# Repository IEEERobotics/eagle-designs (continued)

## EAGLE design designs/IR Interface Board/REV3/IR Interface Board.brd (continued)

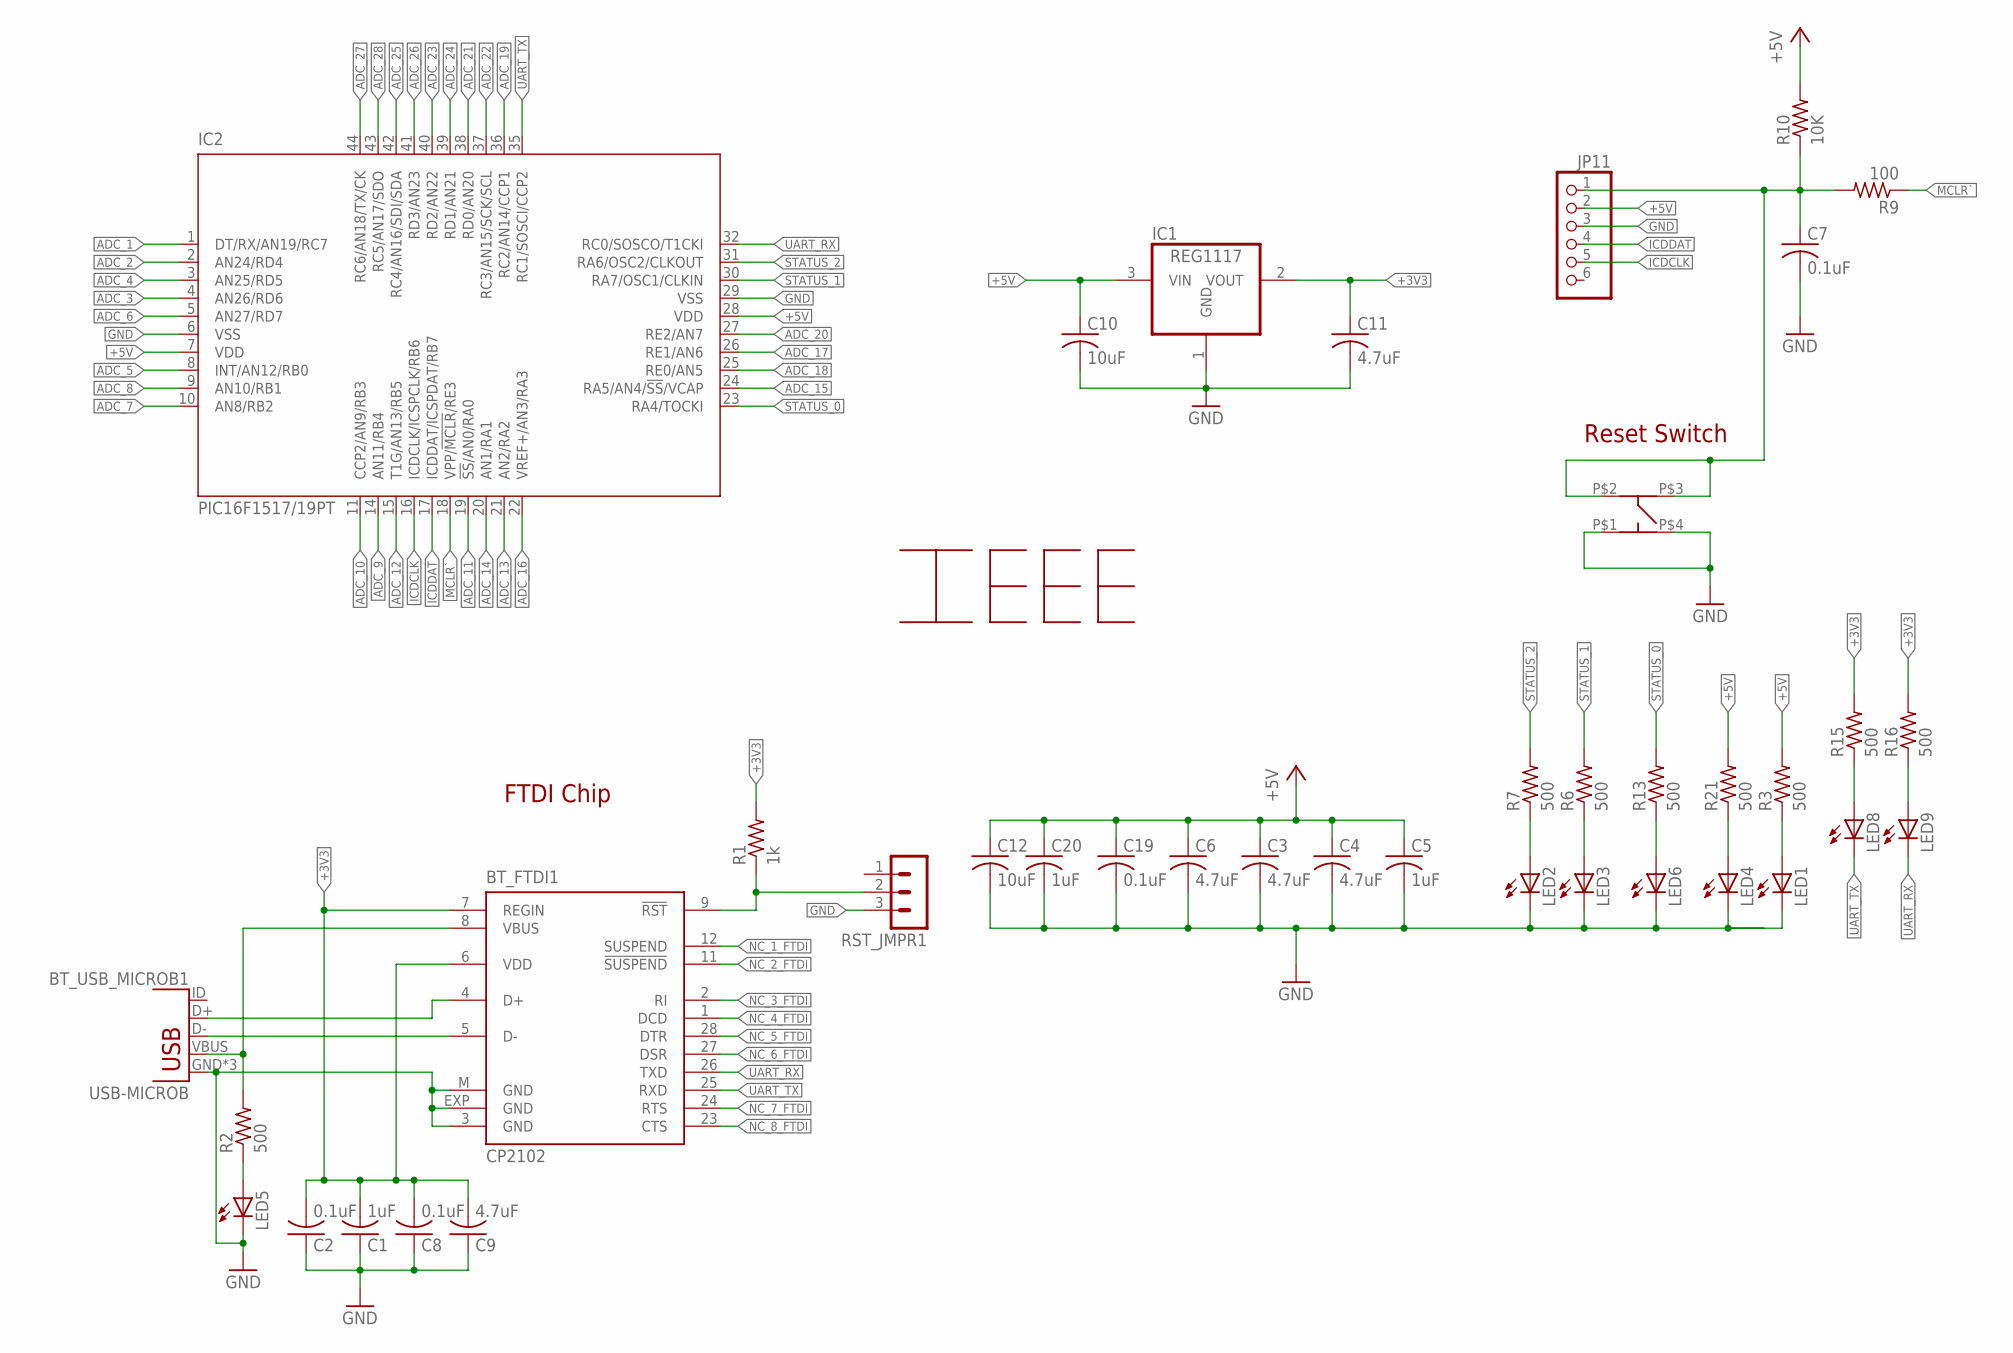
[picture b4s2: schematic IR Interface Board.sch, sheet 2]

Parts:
BT_FTDI1: CP2102; MLP28
BT_USB_MICROB1: USB-MICROB
C1, C5, C20: 1uF; C0805
C2, C7, C8, C19: 0.1uF; C0805
C3, C4, C6, C9, C11: 4.7uF; C0805
C10, C12: 10uF; C0805
IC1: REG1117; SOT223
IC2: PIC16F1517/19PT; TQFP44
JP11: PINHD-1X6/90; 1X06/90
LED1, LED2, LED3, LED4, LED5, LED6, LED8, LED9: LEDSML0603; SML0603
R1: 1k; R0805
R2, R3, R6, R7, R13, R15, R16, R21: 500; R0805
R9: 100; R0805
R10: 10K; R0805
RST_JMPR1: MA03-1
TOUCH_RESET: RESET; MC32882_FINAL
U$1: LOGO; IEEE-LOGO

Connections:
+3V3: BT_FTDI1.6 (VDD), BT_FTDI1.7 (REGIN), C1.2, C2.2, C8.2, C9.2, C11.1, IC1.2 (VOUT), R1.2, R15.2, R16.2
+5V: C3.1, C4.1, C5.1, C6.1, C10.1, C12.1, C19.1, C20.1, IC1.3 (VIN), IC2.7 (VDD), IC2.28 (VDD), JP11.2, R3.2, R10.2, R21.2; also elsewhere on the board
ADC_1: IC2.1 (DT/RX/AN19/RC7); also elsewhere on the board
ADC_2: IC2.2 (AN24/RD4); also elsewhere on the board
ADC_3: IC2.4 (AN26/RD6); also elsewhere on the board
ADC_4: IC2.3 (AN25/RD5); also elsewhere on the board
ADC_5: IC2.8 (INT/AN12/RB0); also elsewhere on the board
ADC_6: IC2.5 (AN27/RD7); also elsewhere on the board
ADC_7: IC2.10 (AN8/RB2); also elsewhere on the board
ADC_8: IC2.9 (AN10/RB1); also elsewhere on the board
ADC_9: IC2.14 (AN11/RB4); also elsewhere on the board
ADC_10: IC2.11 (CCP2/AN9/RB3); also elsewhere on the board
ADC_11: IC2.19 (!SS!/AN0/RA0); also elsewhere on the board
ADC_12: IC2.15 (T1G/AN13/RB5); also elsewhere on the board
ADC_13: IC2.21 (AN2/RA2); also elsewhere on the board
ADC_14: IC2.20 (AN1/RA1); also elsewhere on the board
ADC_15: IC2.24 (RA5/AN4/!SS!/VCAP); also elsewhere on the board
ADC_16: IC2.22 (VREF+/AN3/RA3); also elsewhere on the board
ADC_17: IC2.26 (RE1/AN6); also elsewhere on the board
ADC_18: IC2.25 (RE0/AN5); also elsewhere on the board
ADC_19: IC2.36 (RC2/AN14/CCP1); also elsewhere on the board
ADC_20: IC2.27 (RE2/AN7); also elsewhere on the board
ADC_21: IC2.38 (RD0/AN20); also elsewhere on the board
ADC_22: IC2.37 (RC3/AN15/SCK/SCL); also elsewhere on the board
ADC_23: IC2.40 (RD2/AN22); also elsewhere on the board
ADC_24: IC2.39 (RD1/AN21); also elsewhere on the board
ADC_25: IC2.42 (RC4/AN16/SDI/SDA); also elsewhere on the board
ADC_26: IC2.41 (RD3/AN23); also elsewhere on the board
ADC_27: IC2.44 (RC6/AN18/TX/CK); also elsewhere on the board
ADC_28: IC2.43 (RC5/AN17/SDO); also elsewhere on the board
BT_D+1: BT_FTDI1.4 (D+), BT_USB_MICROB1.D+
BT_D-1: BT_FTDI1.5 (D-), BT_USB_MICROB1.D-
GND: BT_FTDI1.3 (GND), BT_FTDI1.EXP (GND), BT_FTDI1.M (GND), BT_USB_MICROB1.GND, BT_USB_MICROB1.MT1 (GND), BT_USB_MICROB1.MT2 (GND), C1.1, C2.1, C3.2, C4.2, C5.2, C6.2, C7.2, C8.1, C9.1, C10.2, C11.2, C12.2, C19.2, C20.2, IC1.1 (GND), IC2.6 (VSS), IC2.29 (VSS), JP11.3, LED1.C, LED2.C, LED3.C, LED4.C, LED5.C, LED6.C, RST_JMPR1.3, TOUCH_RESET.P$1 (P1), TOUCH_RESET.P$4 (P4); also elsewhere on the board
ICDCLK: IC2.16 (ICDCLK/ICSPCLK/RB6), JP11.5
ICDDAT: IC2.17 (ICDDAT/ICSPDAT/RB7), JP11.4
MCLR: C7.1, JP11.1, R9.2, R10.1, TOUCH_RESET.P$2 (P2), TOUCH_RESET.P$3 (P3)
MCLR`: IC2.18 (VPP/!MCLR!/RE3), R9.1
unnamed: LED3.A, R6.1
unnamed: BT_FTDI1.9 (!RST), R1.1, RST_JMPR1.2
unnamed: LED6.A, R13.1
unnamed: LED1.A, R3.1
unnamed: LED2.A, R7.1
unnamed: LED4.A, R21.1
unnamed: LED8.A, R15.1
unnamed: LED9.A, R16.1
unnamed: LED5.A, R2.1
NC_1_FTDI: BT_FTDI1.12 (SUSPEND)
NC_2_FTDI: BT_FTDI1.11 (!SUSPEND)
NC_3_FTDI: BT_FTDI1.2 (RI)
NC_4_FTDI: BT_FTDI1.1 (DCD)
NC_5_FTDI: BT_FTDI1.28 (DTR)
NC_6_FTDI: BT_FTDI1.27 (DSR)
NC_7_FTDI: BT_FTDI1.24 (RTS)
NC_8_FTDI: BT_FTDI1.23 (CTS)
STATUS_0: IC2.23 (RA4/TOCKI), R13.2
STATUS_1: IC2.30 (RA7/OSC1/CLKIN), R6.2
STATUS_2: IC2.31 (RA6/OSC2/CLKOUT), R7.2
UART_RX: BT_FTDI1.26 (TXD), IC2.32 (RC0/SOSCO/T1CKI), LED9.C
UART_TX: BT_FTDI1.25 (RXD), IC2.35 (RC1/SOSCI/CCP2), LED8.C
VBUS: BT_FTDI1.8 (VBUS), BT_USB_MICROB1.VBUS, R2.2; also elsewhere on the board

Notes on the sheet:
Reset Switch
FTDI Chip

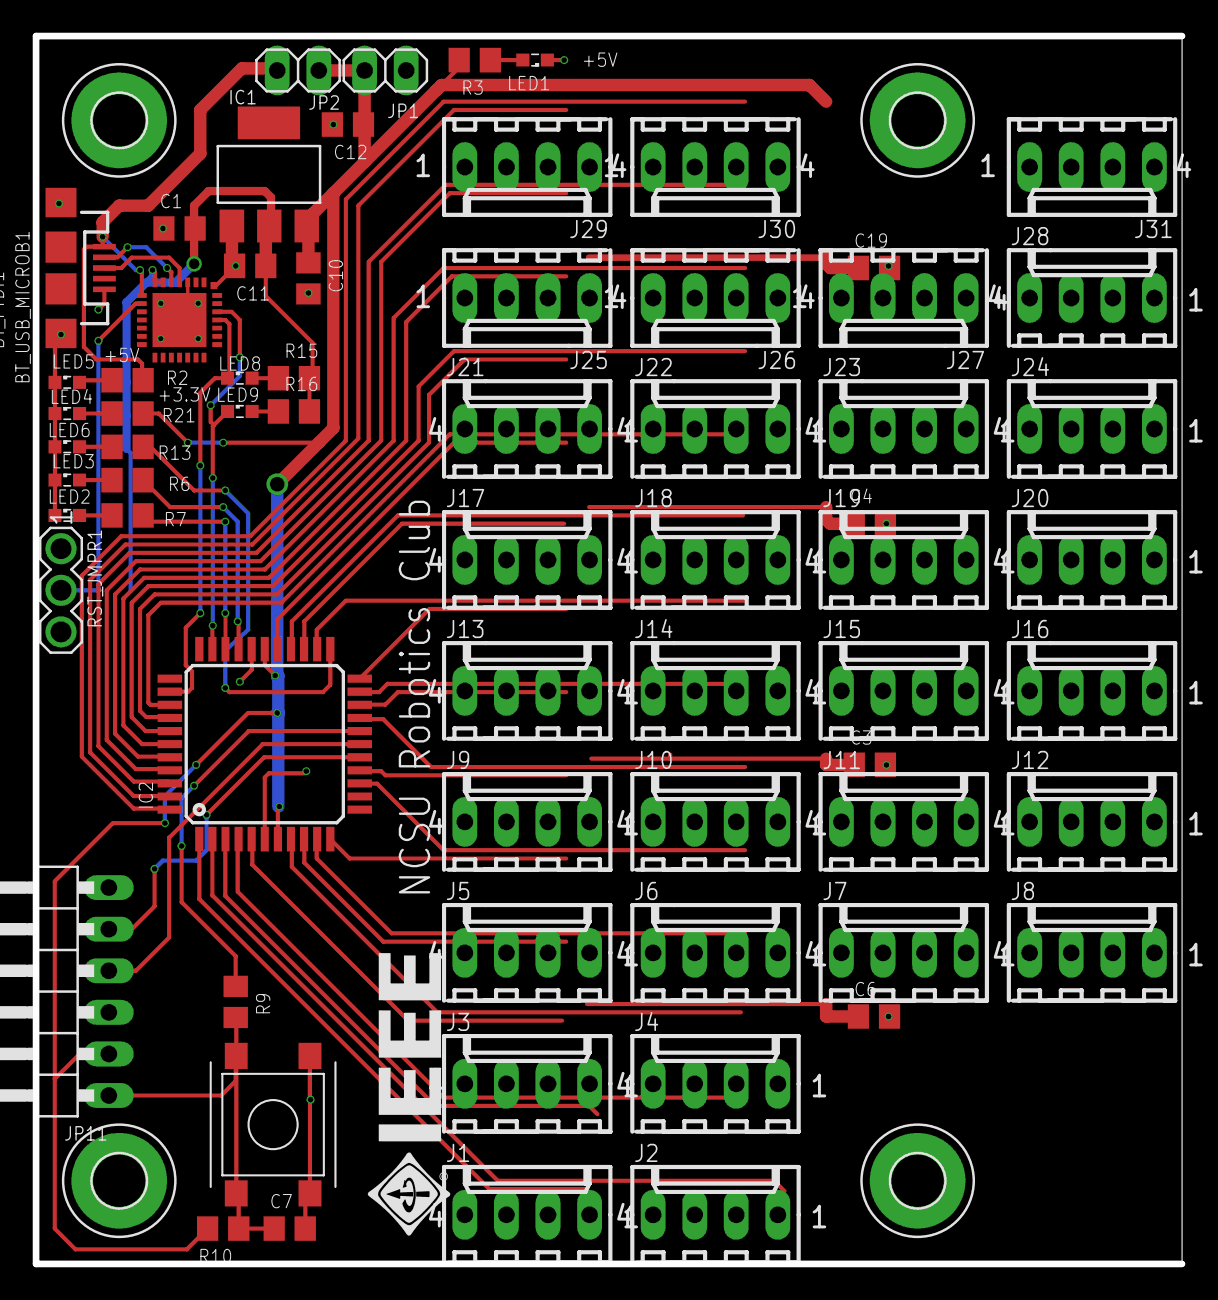
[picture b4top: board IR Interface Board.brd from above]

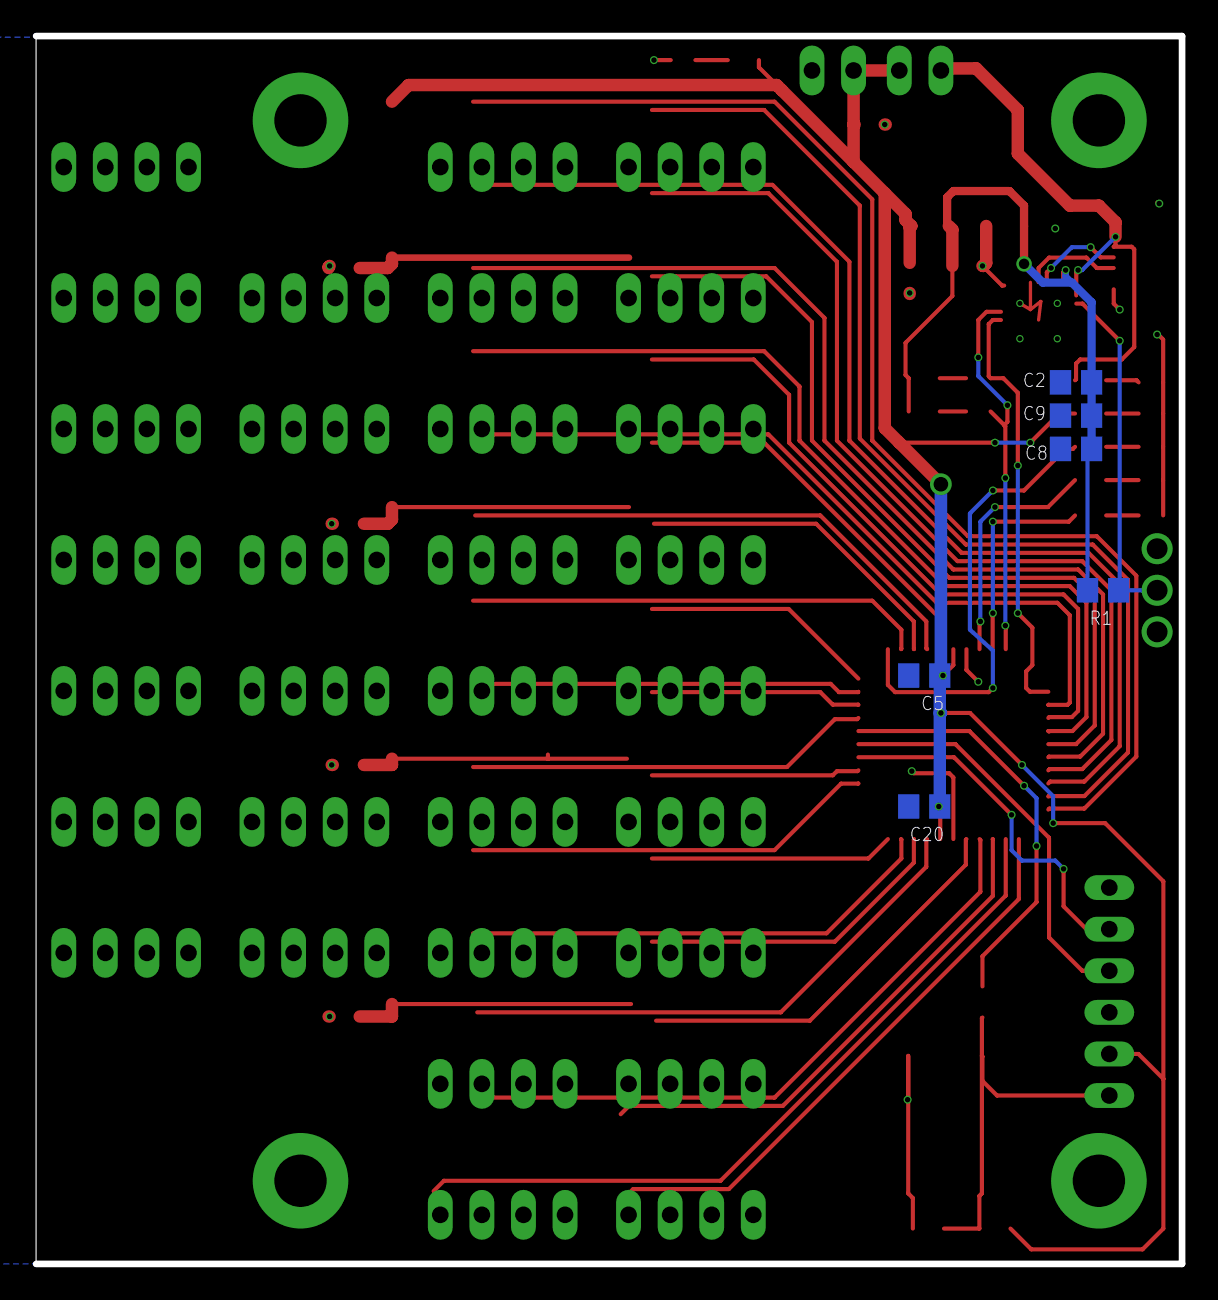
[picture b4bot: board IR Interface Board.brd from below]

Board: 2 copper layers, 70.0 x 75.0 mm, 78 parts (6 on the bottom side), 52 nets.

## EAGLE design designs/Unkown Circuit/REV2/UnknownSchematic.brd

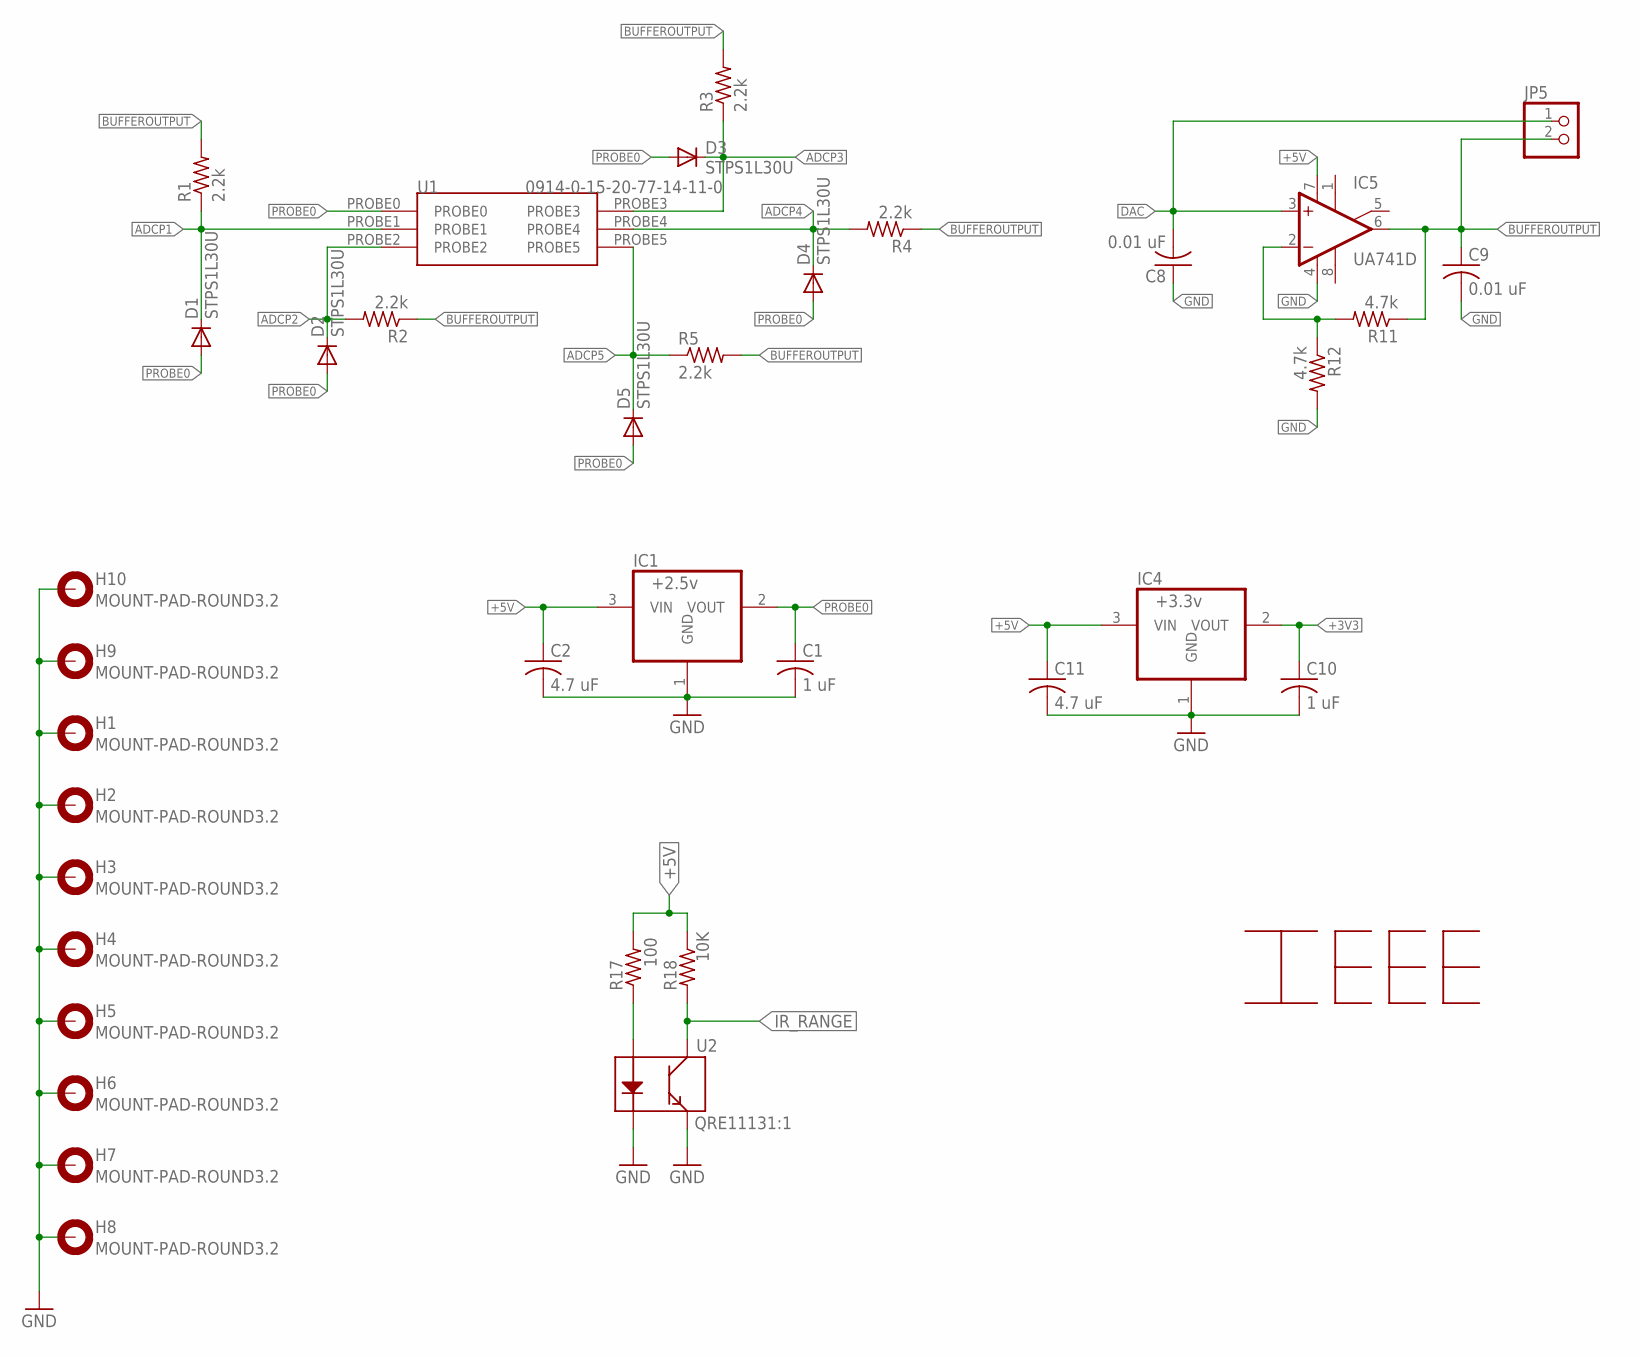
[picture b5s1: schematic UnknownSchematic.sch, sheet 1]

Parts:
C1, C10: 1 uF; C0805
C2, C11: 4.7 uF; C0805
C8, C9: 0.01 uF; C0805
D1, D2, D3, D4, D5: STPS1L30U; DO214AA
H1, H2, H3, H4, H5, H6, H7, H8, H9, H10: MOUNT-PAD-ROUND3.2; 3,2-PAD
IC1: +2.5v; SOT223
IC4: +3.3v; SOT223
IC5: UA741D; SO08
JP5: PINHD-1X2; 1X02
R1, R2, R3, R4, R5: 2.2k; R0805
R11, R12: 4.7k; R0805
R17: 100; R0805
R18: 10K; R0805
U1: 0914-0-15-20-77-14-11-0; HOLE
U2: QRE11131:1; QRE1113-1:1
U$1: LOGO; IEEE-LOGO

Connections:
+3V3: C10.1, IC4.2 (VOUT); also elsewhere on the board
+5V: C2.1, C11.1, IC1.3 (VIN), IC4.3 (VIN), IC5.7 (V+), R17.2, R18.1; also elsewhere on the board
ADCP1: D1.C, R1.1, U1.PROBE1; also elsewhere on the board
ADCP2: D2.C, R2.2, U1.PROBE2; also elsewhere on the board
ADCP3: D3.C, R3.1, U1.PROBE3; also elsewhere on the board
ADCP4: D4.C, R4.2, U1.PROBE4; also elsewhere on the board
ADCP5: D5.C, R5.1, U1.PROBE5; also elsewhere on the board
BUFFEROUTPUT: C9.1, IC5.6 (OUT), JP5.2, R1.2, R2.1, R3.2, R4.1, R5.2, R11.1
DAC: C8.2, IC5.3 (+IN), JP5.1; also elsewhere on the board
GND: C1.2, C2.2, C8.1, C9.2, C10.2, C11.2, H1.B3,2, H2.B3,2, H3.B3,2, H4.B3,2, H5.B3,2, H6.B3,2, H7.B3,2, H8.B3,2, H9.B3,2, H10.B3,2, IC1.1 (GND), IC4.1 (GND), IC5.4 (V-), R12.2, U2.2 (K), U2.4 (E); also elsewhere on the board
IR_RANGE: R18.2, U2.3 (C); also elsewhere on the board
unnamed: IC5.2 (-IN), R11.2, R12.1
unnamed: R17.1, U2.1 (A)
PROBE0: C1.1, D1.A, D2.A, D3.A, D4.A, D5.A, IC1.2 (VOUT), U1.PROBE0; also elsewhere on the board

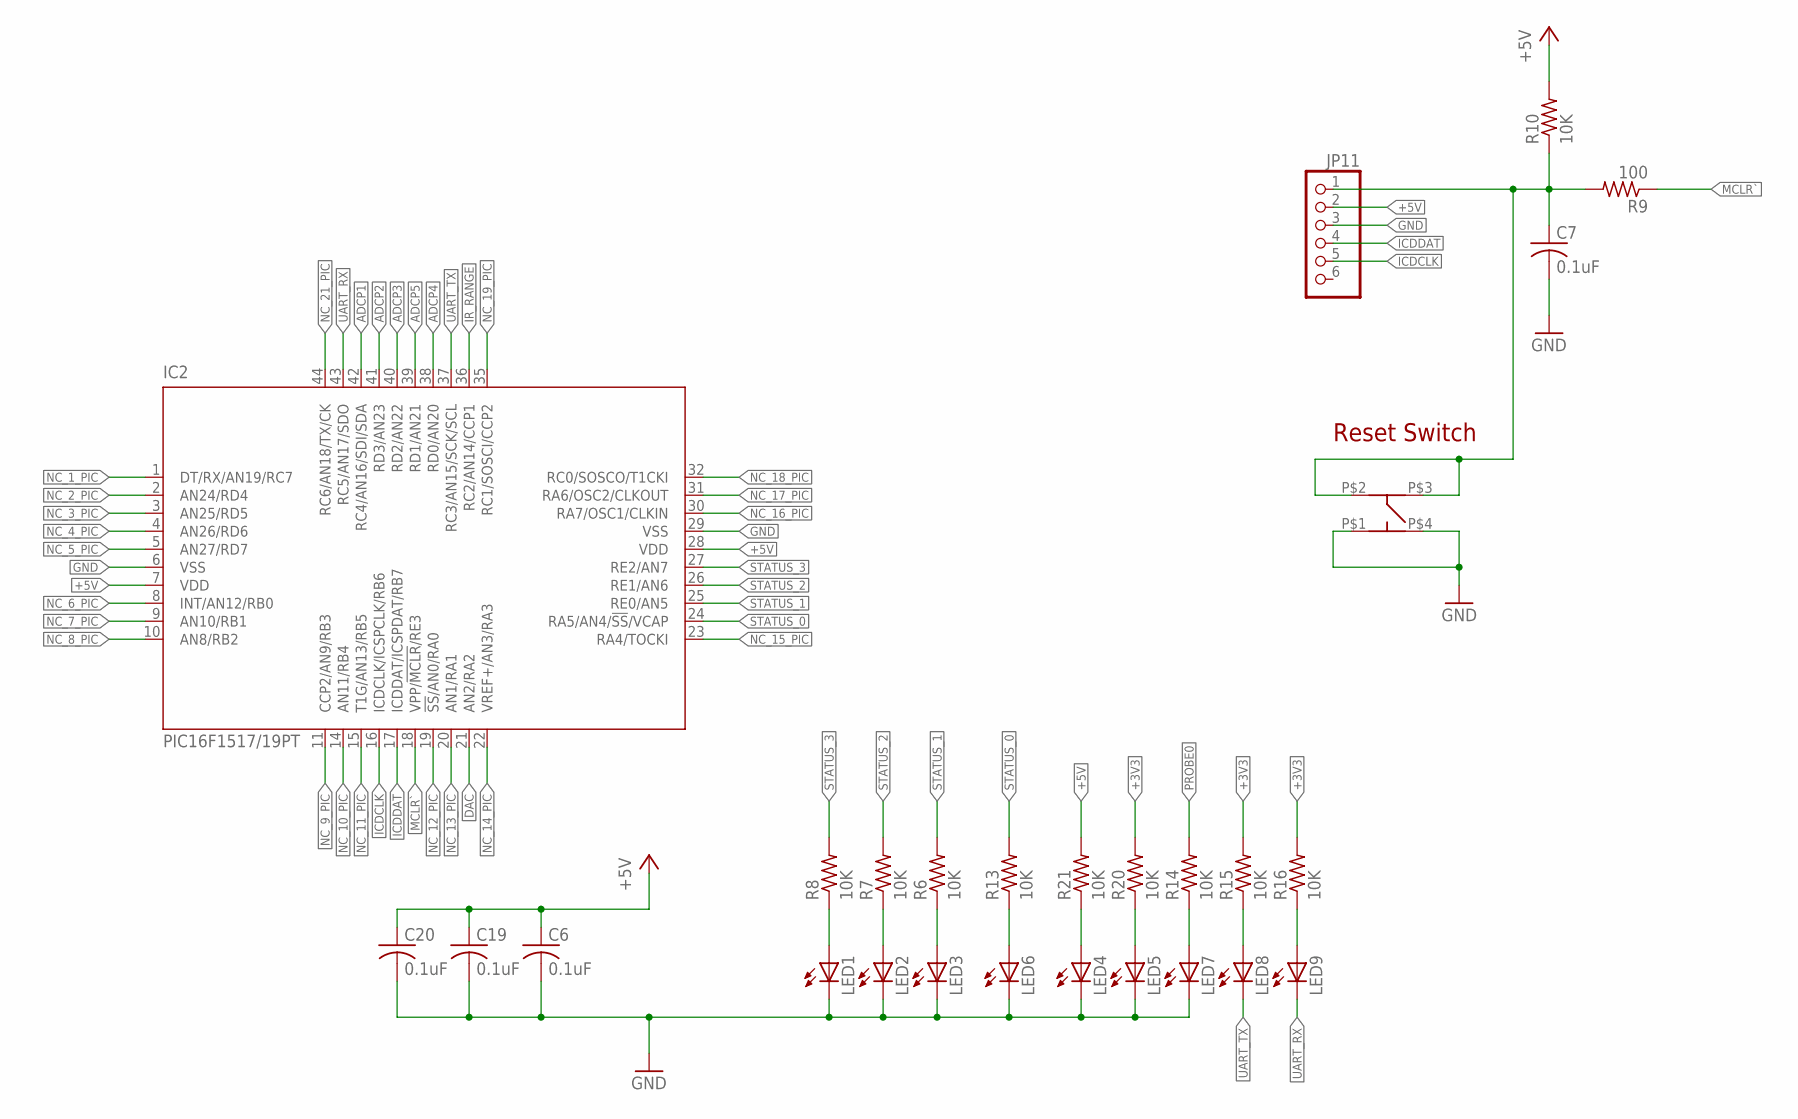
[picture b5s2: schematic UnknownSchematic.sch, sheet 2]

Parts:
C6, C7, C19, C20: 0.1uF; C0805
IC2: PIC16F1517/19PT; TQFP44
JP11: PINHD-1X6/90; 1X06/90
LED1, LED2, LED3, LED4, LED5, LED6, LED7, LED8, LED9: LEDSML0603; SML0603
R6, R7, R8, R13, R14, R15, R16, R20, R21: 10K; R0805
R9: 100; R1206
R10: 10K; R1206
TOUCH_RESET: RESET; MC32882_FINAL

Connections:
+3V3: R15.2, R16.2, R20.2; also elsewhere on the board
+5V: C6.1, C19.1, C20.1, IC2.7 (VDD), IC2.28 (VDD), JP11.2, R10.2, R21.2; also elsewhere on the board
ADCP1: IC2.42 (RC4/AN16/SDI/SDA); also elsewhere on the board
ADCP2: IC2.41 (RD3/AN23); also elsewhere on the board
ADCP3: IC2.40 (RD2/AN22); also elsewhere on the board
ADCP4: IC2.38 (RD0/AN20); also elsewhere on the board
ADCP5: IC2.39 (RD1/AN21); also elsewhere on the board
DAC: IC2.21 (AN2/RA2); also elsewhere on the board
GND: C6.2, C7.2, C19.2, C20.2, IC2.6 (VSS), IC2.29 (VSS), JP11.3, LED1.C, LED2.C, LED3.C, LED4.C, LED5.C, LED6.C, LED7.C, TOUCH_RESET.P$1 (P1), TOUCH_RESET.P$4 (P4); also elsewhere on the board
ICDCLK: IC2.16 (ICDCLK/ICSPCLK/RB6), JP11.5
ICDDAT: IC2.17 (ICDDAT/ICSPDAT/RB7), JP11.4
IR_RANGE: IC2.36 (RC2/AN14/CCP1); also elsewhere on the board
MCLR: C7.1, JP11.1, R9.2, R10.1, TOUCH_RESET.P$2 (P2), TOUCH_RESET.P$3 (P3)
MCLR`: IC2.18 (VPP/!MCLR!/RE3), R9.1
unnamed: LED3.A, R6.1
unnamed: LED6.A, R13.1
unnamed: LED7.A, R14.1
unnamed: LED5.A, R20.1
unnamed: LED2.A, R7.1
unnamed: LED1.A, R8.1
unnamed: LED4.A, R21.1
unnamed: LED8.A, R15.1
unnamed: LED9.A, R16.1
NC_1_PIC: IC2.1 (DT/RX/AN19/RC7)
NC_2_PIC: IC2.2 (AN24/RD4)
NC_3_PIC: IC2.3 (AN25/RD5)
NC_4_PIC: IC2.4 (AN26/RD6)
NC_5_PIC: IC2.5 (AN27/RD7)
NC_6_PIC: IC2.8 (INT/AN12/RB0)
NC_7_PIC: IC2.9 (AN10/RB1)
NC_8_PIC: IC2.10 (AN8/RB2)
NC_9_PIC: IC2.11 (CCP2/AN9/RB3)
NC_10_PIC: IC2.14 (AN11/RB4)
NC_11_PIC: IC2.15 (T1G/AN13/RB5)
NC_12_PIC: IC2.19 (!SS!/AN0/RA0)
NC_13_PIC: IC2.20 (AN1/RA1)
NC_14_PIC: IC2.22 (VREF+/AN3/RA3)
NC_15_PIC: IC2.23 (RA4/TOCKI)
NC_16_PIC: IC2.30 (RA7/OSC1/CLKIN)
NC_17_PIC: IC2.31 (RA6/OSC2/CLKOUT)
NC_18_PIC: IC2.32 (RC0/SOSCO/T1CKI)
NC_19_PIC: IC2.35 (RC1/SOSCI/CCP2)
NC_21_PIC: IC2.44 (RC6/AN18/TX/CK)
PROBE0: R14.2; also elsewhere on the board
STATUS_0: IC2.24 (RA5/AN4/!SS!/VCAP), R13.2
STATUS_1: IC2.25 (RE0/AN5), R6.2
STATUS_2: IC2.26 (RE1/AN6), R7.2
STATUS_3: IC2.27 (RE2/AN7), R8.2
UART_RX: IC2.43 (RC5/AN17/SDO), LED9.C; also elsewhere on the board
UART_TX: IC2.37 (RC3/AN15/SCK/SCL), LED8.C; also elsewhere on the board

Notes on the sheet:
Reset Switch

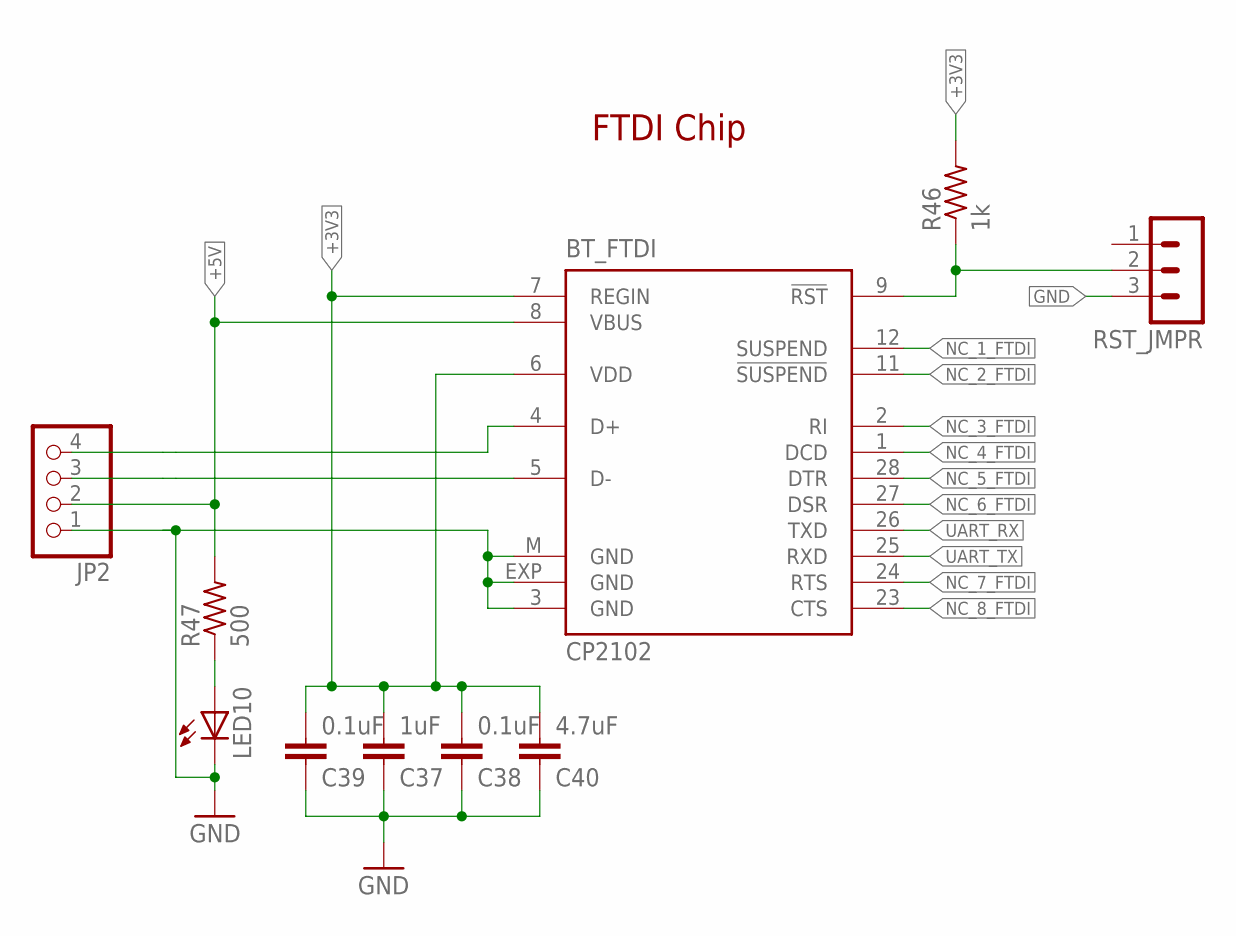
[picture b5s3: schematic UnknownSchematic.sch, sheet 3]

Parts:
BT_FTDI: CP2102; MLP28
C37: 1uF; C0805
C38, C39: 0.1uF; C0805
C40: 4.7uF; C0805
JP2: PINHD-1X4; 1X04
LED10: LEDSML0603; SML0603
R46: 1k; R0805
R47: 500; R0805
RST_JMPR: MA03-1

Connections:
+3V3: BT_FTDI.6 (VDD), BT_FTDI.7 (REGIN), C37.2, C38.2, C39.2, C40.2, R46.2; also elsewhere on the board
+5V: BT_FTDI.8 (VBUS), JP2.2, R47.2; also elsewhere on the board
BT_D+: BT_FTDI.4 (D+), JP2.4
BT_D-: BT_FTDI.5 (D-), JP2.3
GND: BT_FTDI.3 (GND), BT_FTDI.EXP (GND), BT_FTDI.M (GND), C37.1, C38.1, C39.1, C40.1, JP2.1, LED10.C, RST_JMPR.3; also elsewhere on the board
unnamed: LED10.A, R47.1
unnamed: BT_FTDI.9 (!RST), R46.1, RST_JMPR.2
NC_1_FTDI: BT_FTDI.12 (SUSPEND)
NC_2_FTDI: BT_FTDI.11 (!SUSPEND)
NC_3_FTDI: BT_FTDI.2 (RI)
NC_4_FTDI: BT_FTDI.1 (DCD)
NC_5_FTDI: BT_FTDI.28 (DTR)
NC_6_FTDI: BT_FTDI.27 (DSR)
NC_7_FTDI: BT_FTDI.24 (RTS)
NC_8_FTDI: BT_FTDI.23 (CTS)
UART_RX: BT_FTDI.26 (TXD); also elsewhere on the board
UART_TX: BT_FTDI.25 (RXD); also elsewhere on the board

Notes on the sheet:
FTDI Chip

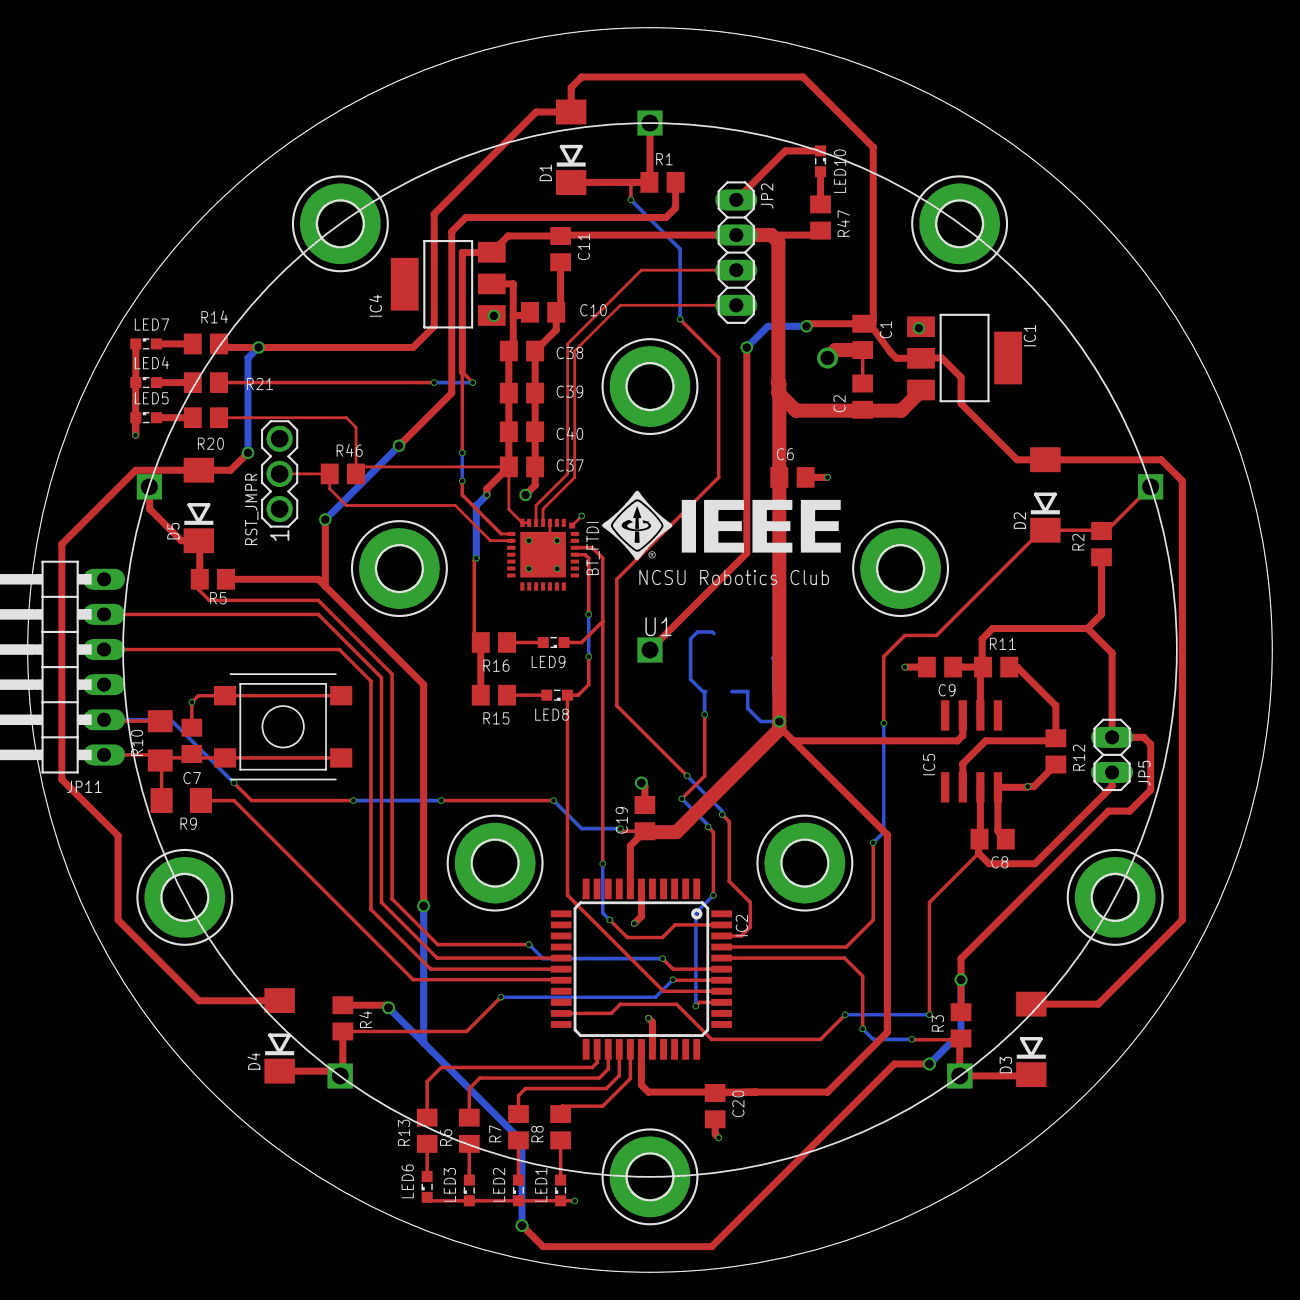
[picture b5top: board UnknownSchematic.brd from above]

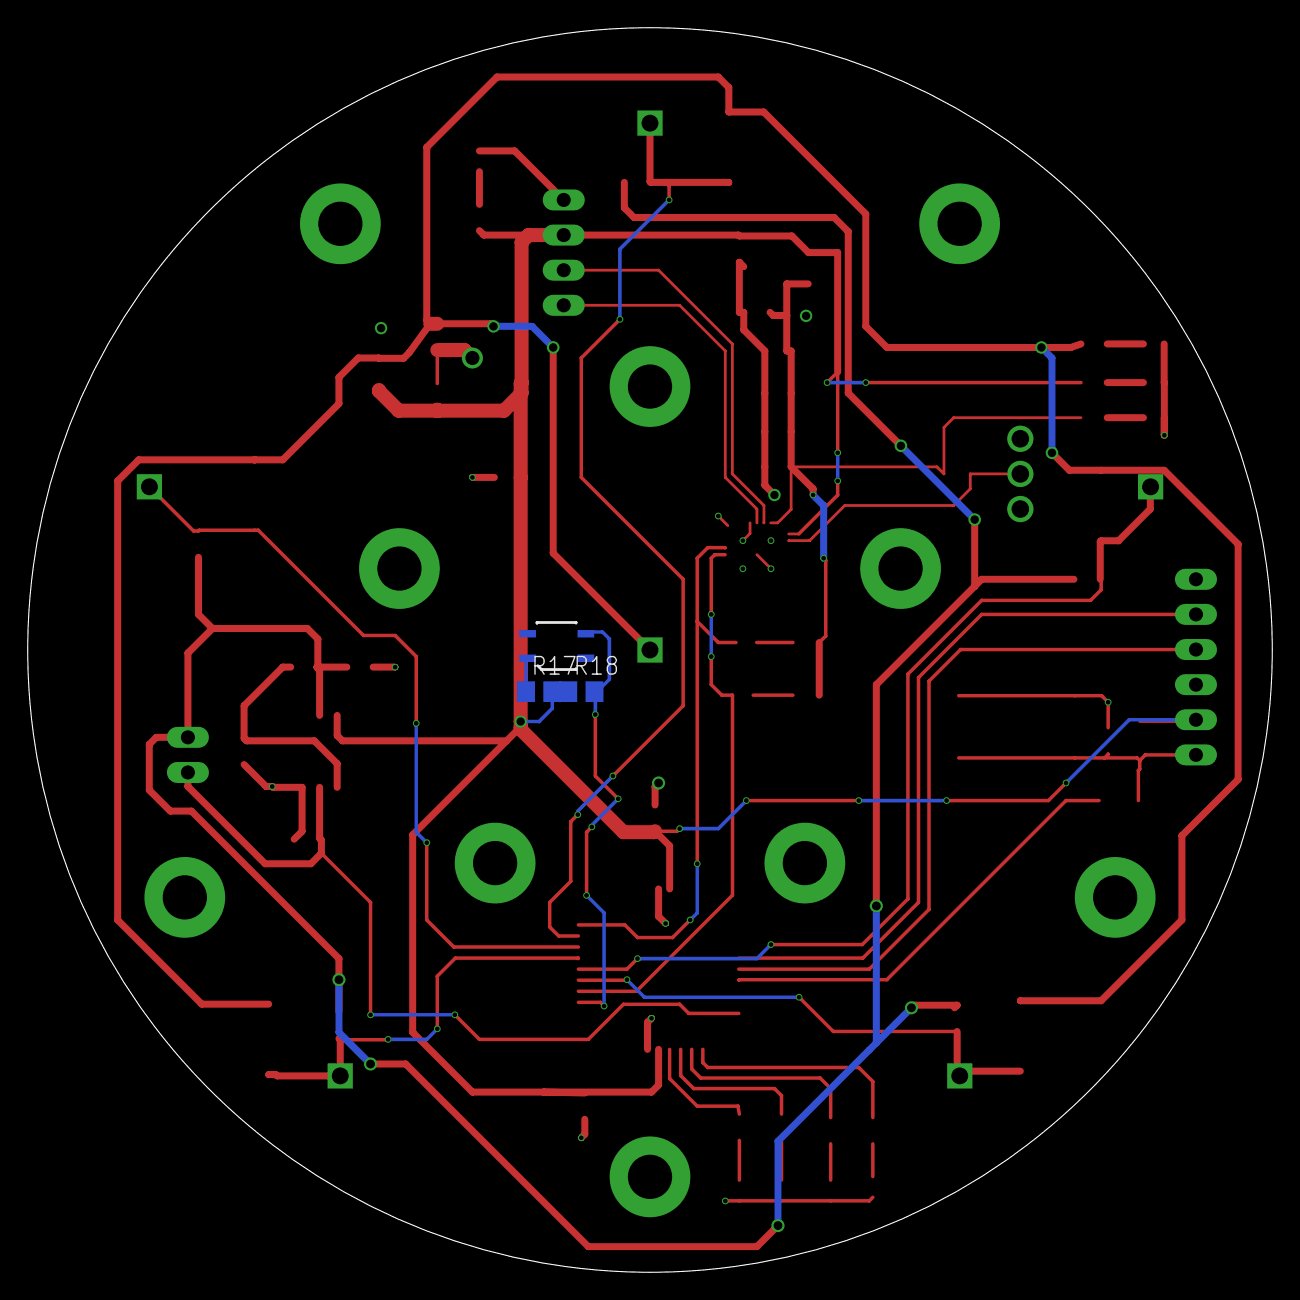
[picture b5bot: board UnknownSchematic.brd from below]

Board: 2 copper layers, 90.0 x 90.0 mm, 74 parts (3 on the bottom side), 37 nets.

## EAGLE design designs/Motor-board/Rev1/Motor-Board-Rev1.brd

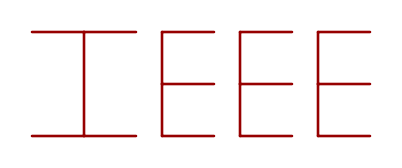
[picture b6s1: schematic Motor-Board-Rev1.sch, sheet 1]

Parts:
U$1: LOGO; IEEE-LOGO
